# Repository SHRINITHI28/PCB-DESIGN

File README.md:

# 🔁 LED Flip-Flop Circuit – PCB Design using KiCad

This repository contains the complete PCB design files for a **LED Flip-Flop circuit** created using **KiCad**. This project demonstrates basic electronics circuit design, schematic creation, PCB layout, and 3D visualization using open-source EDA tools.

---

## 🧩 Project Overview

A **flip-flop LED circuit** alternates two LEDs in an on-off pattern using basic electronic components like **transistors, resistors, and capacitors**. It's a classic beginner-friendly project that teaches timing circuits and PCB design.

---

## 🛠️ Tools Used

- **KiCad** 
- **Gerber Viewer** (for fabrication preview)
- **KiCad 3D Viewer** (for PCB rendering)

---

## 📁 Project Structure

# PCB-DESIGN
LED FLIP FLOP CIRCUIT

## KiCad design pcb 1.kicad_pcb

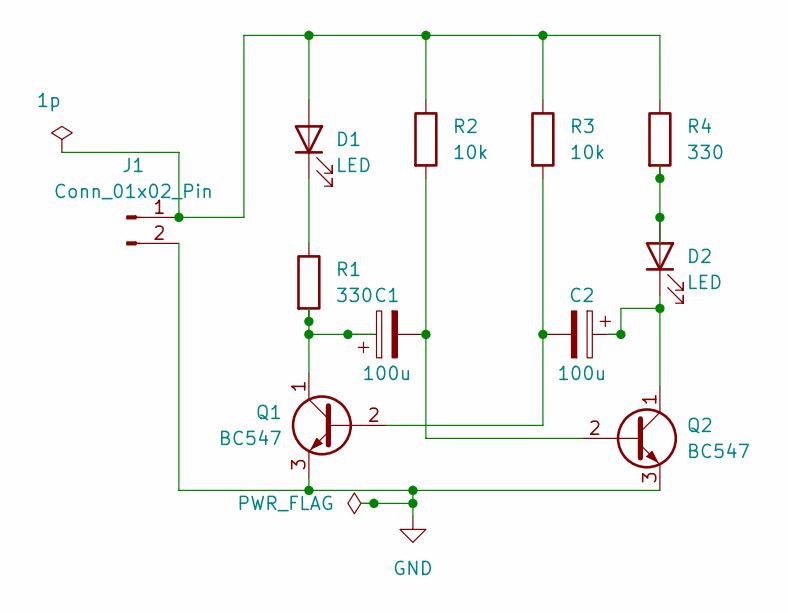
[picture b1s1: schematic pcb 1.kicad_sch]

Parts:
C1, C2: 100u; C_Radial_D10.0mm_H16.0mm_P5.00mm
D1, D2: LED; LED_D5.0mm
J1: Conn_01x02_Pin; PinHeader_1x02_P1.00mm_Vertical
Q1, Q2: BC547; TO-92_Inline
R1: 330
R2, R3: 10k; R_Axial_DIN0204_L3.6mm_D1.6mm_P5.08mm_Horizontal
R4: 330; R_Axial_DIN0204_L3.6mm_D1.6mm_P5.08mm_Horizontal

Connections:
GND: J1.2, Q1.3 (E), Q2.3 (E)
unnamed: D1.2 (A), J1.1, R2.1, R3.1, R4.1
unnamed: D1.1 (K), R1.1
unnamed: D2.2 (A), R4.2
unnamed: C2.1, D2.1 (K), Q2.1 (C)
unnamed: C2.2, Q1.2 (B), R3.2
unnamed: C1.1, Q1.1 (C), R1.2
unnamed: C1.2, Q2.2 (B), R2.2

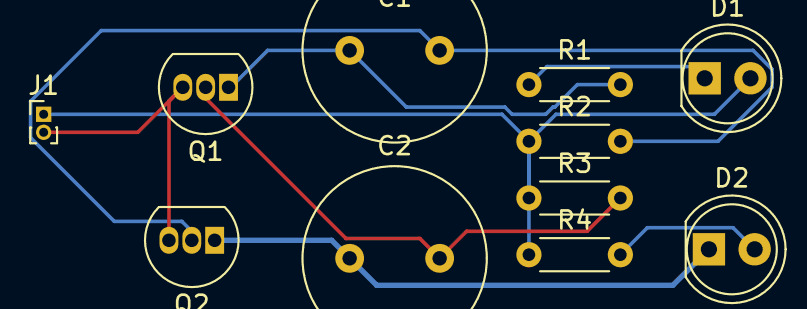
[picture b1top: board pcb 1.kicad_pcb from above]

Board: 2 copper layers, 11 parts (0 on the bottom side), 8 nets.

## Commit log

2025-07-19 Add files via upload
    DRC ERROR CHECK
